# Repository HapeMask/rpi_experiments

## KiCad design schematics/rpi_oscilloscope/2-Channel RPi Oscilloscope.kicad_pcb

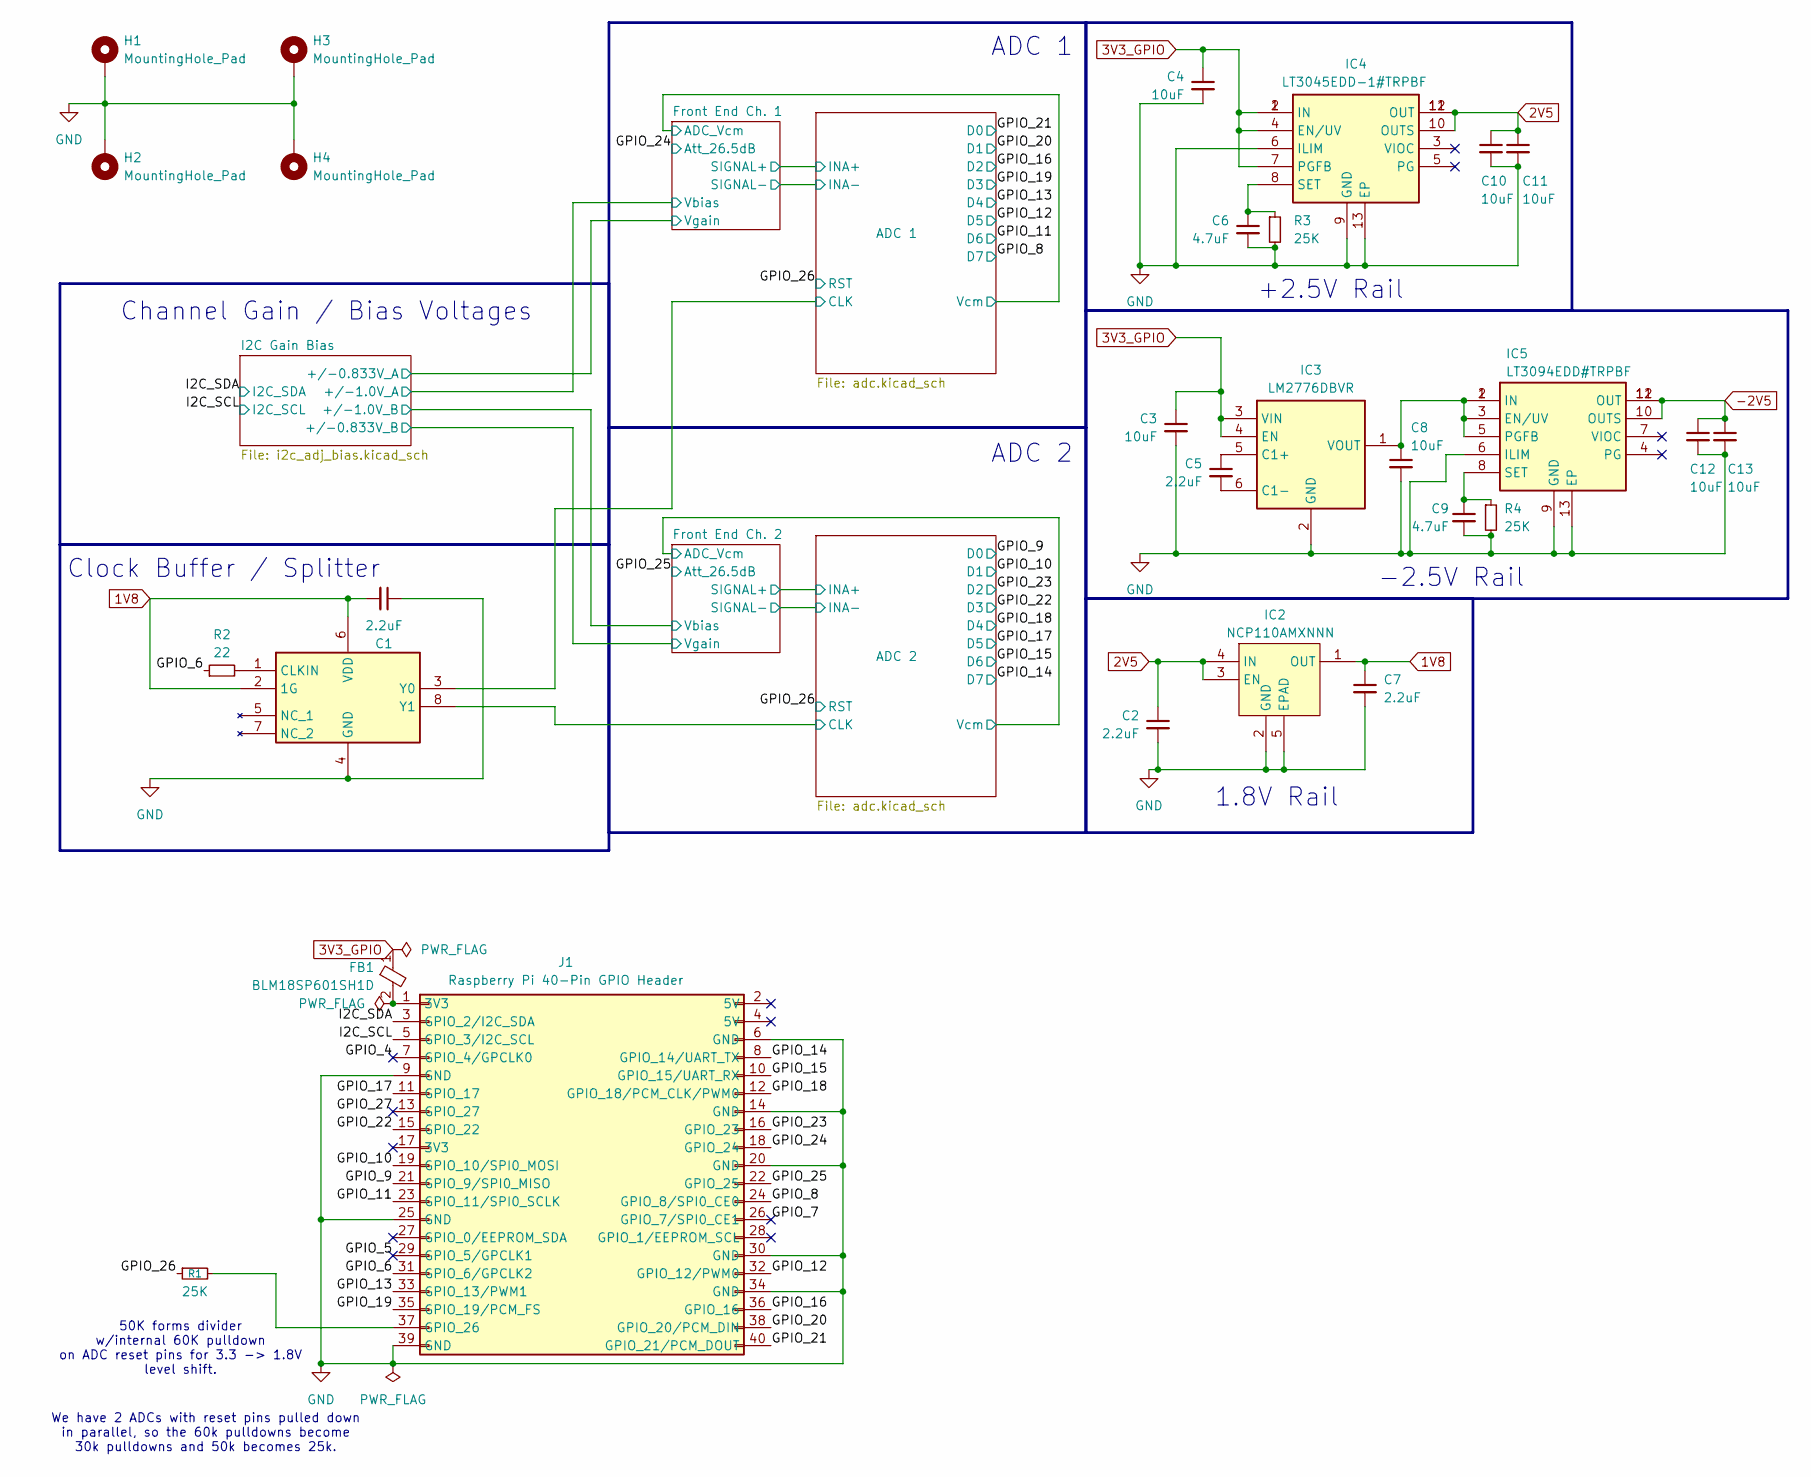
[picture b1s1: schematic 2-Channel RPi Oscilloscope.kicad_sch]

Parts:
C1, C2, C5, C7: 2.2uF; C_0805_2012Metric
C3, C4, C8, C10, C11, C12, C13: 10uF; C_0805_2012Metric; Manufacturer_Part_Number CL21B106KOQNNNE
C6, C9: 4.7uF; C_0805_2012Metric; Manufacturer_Part_Number GRM21BR71C475ME51K
FB1: BLM18SP601SH1D; BLM18SP221SN1B; Manufacturer_Part_Number BLM18SP601SH1D; Mouser Part Number 81-BLM18SP601SH1D
H1, H2, H3, H4: MountingHole_Pad; MountingHole_3mm_Pad_TopBottom
IC1: LMK1C1102PWR; SOP65P640X120-8N; Manufacturer_Part_Number LMK1C1102PWR; Mouser Part Number 595-LMK1C1102PWR
IC2: NCP110AMXNNN; OnSemi_XDFN4-1EP_1.0x1.0mm_EP0.52x0.52mm; Manufacturer_Part_Number NCP110AMX180TBG
IC3: LM2776DBVR; SOT95P280X145-6N; Manufacturer_Part_Number LM2776DBVR; Mouser Part Number 595-LM2776DBVR
IC4: LT3045EDD-1#TRPBF; SON45P300X300X80-13N-D; Manufacturer_Part_Number LT3045EDD-1#TRPBF; Mouser Part Number 584-LT3045EDD-1TRPBF
IC5: LT3094EDD#TRPBF; SON45P300X300X80-13N-D; Manufacturer_Part_Number LT3094EDD#TRPBF; Mouser Part Number 584-LT3094EDD#TRPBF
J1: Raspberry Pi 40-Pin GPIO Header; PinSocket_2x20_P2.54mm_Vertical
R1: 25K; R_0805_2012Metric
R2: 22; R_0805_2012Metric; Manufacturer_Part_Number RS73G2ATTD22R0B
R3, R4: 25K; R_0805_2012Metric; Manufacturer_Part_Number CPF-A-0805B25KE

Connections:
1V8: C1.2, C7.1, IC1.2 (1G), IC1.6 (VDD), IC2.1 (OUT); also elsewhere on the board
2V5: C2.1, C10.1, C11.1, IC2.3 (EN), IC2.4 (IN), IC4.10 (OUTS), IC4.11 (OUT), IC4.12 (OUT); also elsewhere on the board
3V3_GPIO: C3.1, C4.1, FB1.1, IC3.3 (VIN), IC3.4 (EN), IC4.1 (IN), IC4.2 (IN), IC4.4 (EN/UV), IC4.7 (PGFB); also elsewhere on the board
-2V5: C12.1, C13.1, IC5.10 (OUTS), IC5.11 (OUT), IC5.12 (OUT); also elsewhere on the board
/ADC 1/CLK: IC1.3 (Y0); also elsewhere on the board
/ADC 2/CLK: IC1.8 (Y1); also elsewhere on the board
/GPIO_4: J1.7 (GPIO_4/GPCLK0)
/GPIO_5: J1.29 (GPIO_5/GPCLK1)
/GPIO_6: J1.31 (GPIO_6/GPCLK2), R2.1
/GPIO_7: J1.26 (GPIO_7/SPI0_CE1)
/GPIO_8: J1.24 (GPIO_8/SPI0_CE0); also elsewhere on the board
/GPIO_9: J1.21 (GPIO_9/SPI0_MISO); also elsewhere on the board
/GPIO_10: J1.19 (GPIO_10/SPI0_MOSI); also elsewhere on the board
/GPIO_11: J1.23 (GPIO_11/SPI0_SCLK); also elsewhere on the board
/GPIO_12: J1.32 (GPIO_12/PWM0); also elsewhere on the board
/GPIO_13: J1.33 (GPIO_13/PWM1); also elsewhere on the board
/GPIO_14: J1.8 (GPIO_14/UART_TX); also elsewhere on the board
/GPIO_15: J1.10 (GPIO_15/UART_RX); also elsewhere on the board
/GPIO_16: J1.36 (GPIO_16); also elsewhere on the board
/GPIO_17: J1.11 (GPIO_17); also elsewhere on the board
/GPIO_18: J1.12 (GPIO_18/PCM_CLK/PWM0); also elsewhere on the board
/GPIO_19: J1.35 (GPIO_19/PCM_FS); also elsewhere on the board
/GPIO_20: J1.38 (GPIO_20/PCM_DIN); also elsewhere on the board
/GPIO_21: J1.40 (GPIO_21/PCM_DOUT); also elsewhere on the board
/GPIO_22: J1.15 (GPIO_22); also elsewhere on the board
/GPIO_23: J1.16 (GPIO_23); also elsewhere on the board
/GPIO_24: J1.18 (GPIO_24); also elsewhere on the board
/GPIO_25: J1.22 (GPIO_25); also elsewhere on the board
/GPIO_26: R1.1; also elsewhere on the board
/GPIO_27: J1.13 (GPIO_27)
/I2C_SCL: J1.5 (GPIO_3/I2C_SCL); also elsewhere on the board
/I2C_SDA: J1.3 (GPIO_2/I2C_SDA); also elsewhere on the board
GND: C1.1, C2.2, C3.2, C4.2, C6.2, C7.2, C8.2, C9.2, C10.2, C11.2, C12.2, C13.2, H1.1, H2.1, H3.1, H4.1, IC1.4 (GND), IC2.2 (GND), IC2.5 (EPAD), IC3.2 (GND), IC4.6 (ILIM), IC4.9 (GND), IC4.13 (EP), IC5.6 (ILIM), IC5.9 (GND), IC5.13 (EP), J1.6 (GND), J1.9 (GND), J1.14 (GND), J1.20 (GND), J1.25 (GND), J1.30 (GND), J1.34 (GND), J1.39 (GND), R3.2, R4.2; also elsewhere on the board
unnamed: FB1.2, J1.1 (3V3)
unnamed: IC1.1 (CLKIN), R2.2
unnamed: C5.1, IC3.5 (C1+)
unnamed: C5.2, IC3.6 (C1-)
unnamed: C8.1, IC3.1 (VOUT), IC5.1 (IN), IC5.2 (IN), IC5.3 (EN/UV), IC5.5 (PGFB)
unnamed: C6.1, IC4.8 (SET), R3.1
unnamed: C9.1, IC5.8 (SET), R4.1
unnamed: J1.37 (GPIO_26), R1.2

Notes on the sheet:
ADC 1
ADC 2
We have 2 ADCs with reset pins pulled down in parallel, so the 60k pulldowns become 30k pulldowns and 50k becomes 25k.
+2.5V Rail
-2.5V Rail
1.8V Rail
50K forms divider w/internal 60K pulldown on ADC reset pins for 3.3 -> 1.8V level shift.
Clock Buffer / Splitter
Channel Gain / Bias Voltages

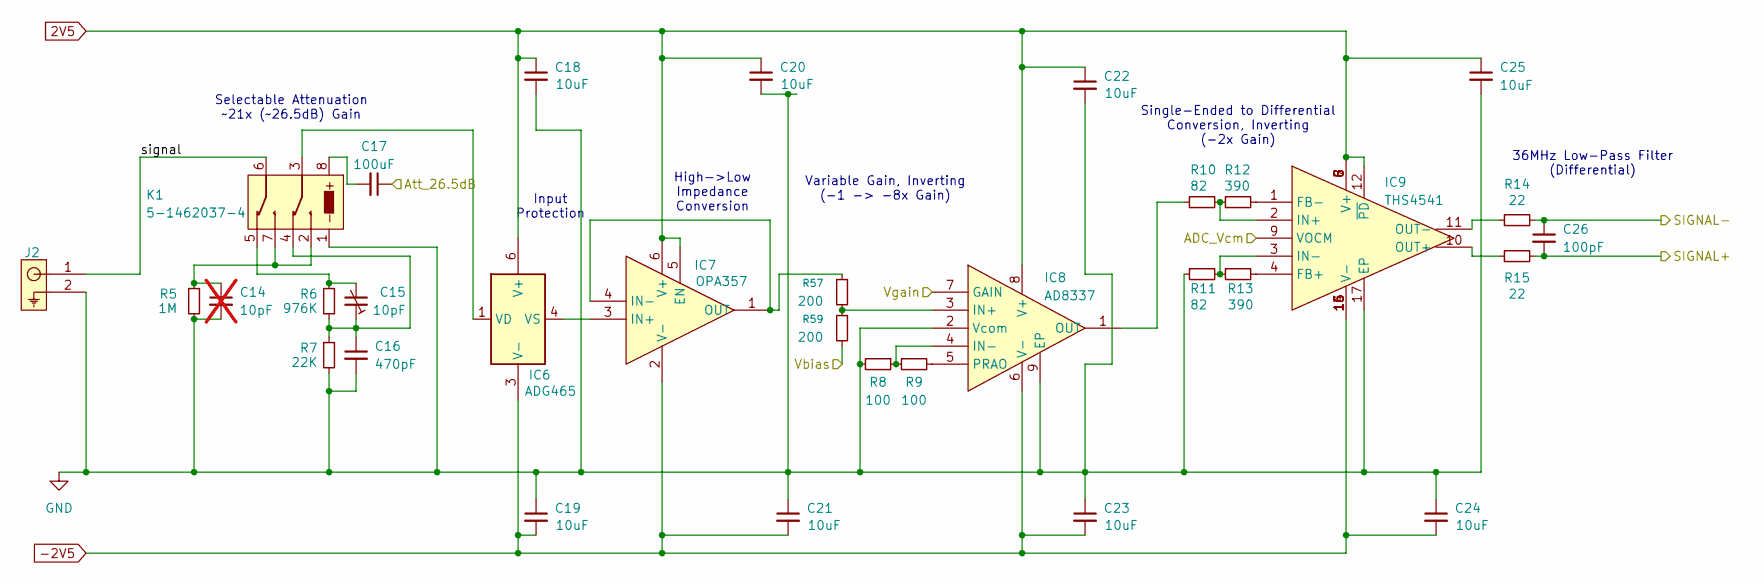
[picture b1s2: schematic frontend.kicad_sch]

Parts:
C14: 10pF; C_0805_2012Metric; not fitted
C15: 10pF; C_Trimmer_Sprague-Goodman_SGC3; Manufacturer_Part_Number SGC3S300
C16: 470pF; C_0805_2012Metric; Manufacturer_Part_Number GRM2165C1H201JA01D
C17: 100uF; C_1206_3216Metric; Manufacturer_Part_Number GRM31CR61A107MEA8L
C18, C19, C20, C21, C22, C23, C24, C25: 10uF; C_0805_2012Metric; Manufacturer_Part_Number CL21B106KOQNNNE
C26: 100pF; C_0805_2012Metric
IC6: ADG465; SOT95P280X145-6N; Manufacturer_Part_Number ADG465BRTZ-REEL7
IC7: OPA357; SOT95P280X145-6N; Manufacturer_Part_Number OPA357AIDBVR; Mouser Part Number 595-OPA357AIDBVR
IC8: AD8337; SON50P300X300X85-9N-D; Manufacturer_Part_Number AD8337BCPZ-REEL7; Mouser Part Number 584-AD8337BCPZ-R7
IC9: THS4541; QFN50P300X300X100-17N-D; Manufacturer_Part_Number THS4541IRGTR; Mouser Part Number 595-THS4541IRGTR
J2: 5-pin Coaxial Connector; 031_5431_10RFX; Manufacturer_Part_Number 031-5431-10RFX
K1: 5-1462037-4; 514620374; Manufacturer_Part_Number 5-1462037-4; Mouser Part Number 655-5-1462037-4
R5: 1M; R_0805_2012Metric
R6: 976K; R_0805_2012Metric
R7: 22K; R_0805_2012Metric
R8, R9: 100; R_0805_2012Metric
R10, R11: 82; R_0805_2012Metric
R12, R13: 390; R_0805_2012Metric
R14, R15: 22; R_0805_2012Metric; Manufacturer_Part_Number RS73G2ATTD22R0B
R57, R59: 200; R_0805_2012Metric

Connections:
2V5: C18.1, C20.1, C22.1, C25.1, IC6.6 (V+), IC7.5 (EN), IC7.6 (V+), IC8.8 (V+), IC9.5 (V+), IC9.6 (V+), IC9.7 (V+), IC9.8 (V+), IC9.12 (~PD); also elsewhere on the board
-2V5: C19.2, C21.2, C23.2, C24.2, IC6.3 (V-), IC7.2 (V-), IC8.6 (V-), IC9.13 (V-), IC9.14 (V-), IC9.15 (V-), IC9.16 (V-); also elsewhere on the board
/ADC 1/INA+: C26.2, R15.2; also elsewhere on the board
/ADC 1/INA-: C26.1, R14.2; also elsewhere on the board
/ADC 1/Vcm: IC9.9 (VOCM); also elsewhere on the board
/Front End Ch. 1/Vbias: R59.2; also elsewhere on the board
/Front End Ch. 1/Vgain: IC8.7 (GAIN); also elsewhere on the board
/Front End Ch. 1/signal: J2.1, K1.6
/GPIO_24: C17.1; also elsewhere on the board
GND: C14.2, C16.2, C18.2, C19.1, C20.2, C21.1, C22.2, C23.1, C24.1, C25.2, IC8.2 (Vcom), IC8.9 (EP), IC9.17 (EP), J2.2, K1.1, R5.2, R7.2, R8.2, R11.1; also elsewhere on the board
unnamed: C14.1, K1.2, K1.7, R5.1
unnamed: C15.1, C16.1, K1.4, R6.2, R7.1
unnamed: C15.2, K1.5, R6.1
unnamed: C17.2, K1.8
unnamed: IC6.1 (VD), K1.3
unnamed: IC6.4 (VS), IC7.3 (IN+)
unnamed: IC7.1 (OUT), IC7.4 (IN-), R57.1
unnamed: IC8.3 (IN+), R57.2, R59.1
unnamed: IC8.4 (IN-), R8.1, R9.1
unnamed: IC8.1 (OUT), R10.1
unnamed: IC8.5 (PRAO), R9.2
unnamed: IC9.4 (FB+), R13.2
unnamed: IC9.1 (FB-), R12.2
unnamed: IC9.2 (IN+), R10.2, R12.1
unnamed: IC9.3 (IN-), R11.2, R13.1
unnamed: IC9.10 (OUT+), R15.1
unnamed: IC9.11 (OUT-), R14.1

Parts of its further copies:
C27: 10pF; C_0805_2012Metric; not fitted
C28: 10pF; C_Trimmer_Sprague-Goodman_SGC3; Manufacturer_Part_Number SGC3S300
C29: 470pF; C_0805_2012Metric; Manufacturer_Part_Number GRM2165C1H201JA01D
C30: 100uF; C_1206_3216Metric; Manufacturer_Part_Number GRM31CR61A107MEA8L
C31, C32, C33, C34, C35, C36, C37, C38: 10uF; C_0805_2012Metric; Manufacturer_Part_Number CL21B106KOQNNNE
C39: 100pF; C_0805_2012Metric
IC10: ADG465; SOT95P280X145-6N; Manufacturer_Part_Number ADG465BRTZ-REEL7
IC11: OPA357; SOT95P280X145-6N; Manufacturer_Part_Number OPA357AIDBVR; Mouser Part Number 595-OPA357AIDBVR
IC12: AD8337; SON50P300X300X85-9N-D; Manufacturer_Part_Number AD8337BCPZ-REEL7; Mouser Part Number 584-AD8337BCPZ-R7
IC13: THS4541; QFN50P300X300X100-17N-D; Manufacturer_Part_Number THS4541IRGTR; Mouser Part Number 595-THS4541IRGTR
J3: 5-pin Coaxial Connector; 031_5431_10RFX; Manufacturer_Part_Number 031-5431-10RFX
K2: 5-1462037-4; 514620374; Manufacturer_Part_Number 5-1462037-4; Mouser Part Number 655-5-1462037-4
R16: 1M; R_0805_2012Metric
R17: 976K; R_0805_2012Metric
R18: 22K; R_0805_2012Metric
R19, R20: 100; R_0805_2012Metric
R21, R22: 82; R_0805_2012Metric
R23, R24: 390; R_0805_2012Metric
R25, R26: 22; R_0805_2012Metric; Manufacturer_Part_Number RS73G2ATTD22R0B
R58, R60: 200; R_0805_2012Metric

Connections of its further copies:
2V5: C31.1, C33.1, C35.1, C38.1, IC10.6 (V+), IC11.5 (EN), IC11.6 (V+), IC12.8 (V+), IC13.5 (V+), IC13.6 (V+), IC13.7 (V+), IC13.8 (V+), IC13.12 (~PD); also elsewhere on the board
-2V5: C32.2, C34.2, C36.2, C37.2, IC10.3 (V-), IC11.2 (V-), IC12.6 (V-), IC13.13 (V-), IC13.14 (V-), IC13.15 (V-), IC13.16 (V-); also elsewhere on the board
/ADC 2/INA+: C39.2, R26.2; also elsewhere on the board
/ADC 2/INA-: C39.1, R25.2; also elsewhere on the board
/ADC 2/Vcm: IC13.9 (VOCM); also elsewhere on the board
/Front End Ch. 2/Vbias: R60.2; also elsewhere on the board
/Front End Ch. 2/Vgain: IC12.7 (GAIN); also elsewhere on the board
/Front End Ch. 2/signal: J3.1, K2.6
/GPIO_25: C30.1; also elsewhere on the board
GND: C27.2, C29.2, C31.2, C32.1, C33.2, C34.1, C35.2, C36.1, C37.1, C38.2, IC12.2 (Vcom), IC12.9 (EP), IC13.17 (EP), J3.2, K2.1, R16.2, R18.2, R19.2, R22.1; also elsewhere on the board
unnamed: C27.1, K2.2, K2.7, R16.1
unnamed: C28.1, C29.1, K2.4, R17.2, R18.1
unnamed: C28.2, K2.5, R17.1
unnamed: C30.2, K2.8
unnamed: IC10.1 (VD), K2.3
unnamed: IC10.4 (VS), IC11.3 (IN+)
unnamed: IC11.1 (OUT), IC11.4 (IN-), R58.1
unnamed: IC12.3 (IN+), R58.2, R60.1
unnamed: IC12.4 (IN-), R19.1, R20.1
unnamed: IC12.1 (OUT), R21.1
unnamed: IC12.5 (PRAO), R20.2
unnamed: IC13.4 (FB+), R24.2
unnamed: IC13.1 (FB-), R23.2
unnamed: IC13.2 (IN+), R21.2, R23.1
unnamed: IC13.3 (IN-), R22.2, R24.1
unnamed: IC13.10 (OUT+), R26.1
unnamed: IC13.11 (OUT-), R25.1

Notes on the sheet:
Input Protection
Single-Ended to Differential Conversion, Inverting (-2x Gain)
High->Low Impedance Conversion
36MHz Low-Pass Filter (Differential)
Selectable Attenuation ~21x (~26.5dB) Gain
Variable Gain, Inverting (-1 -> -8x Gain)

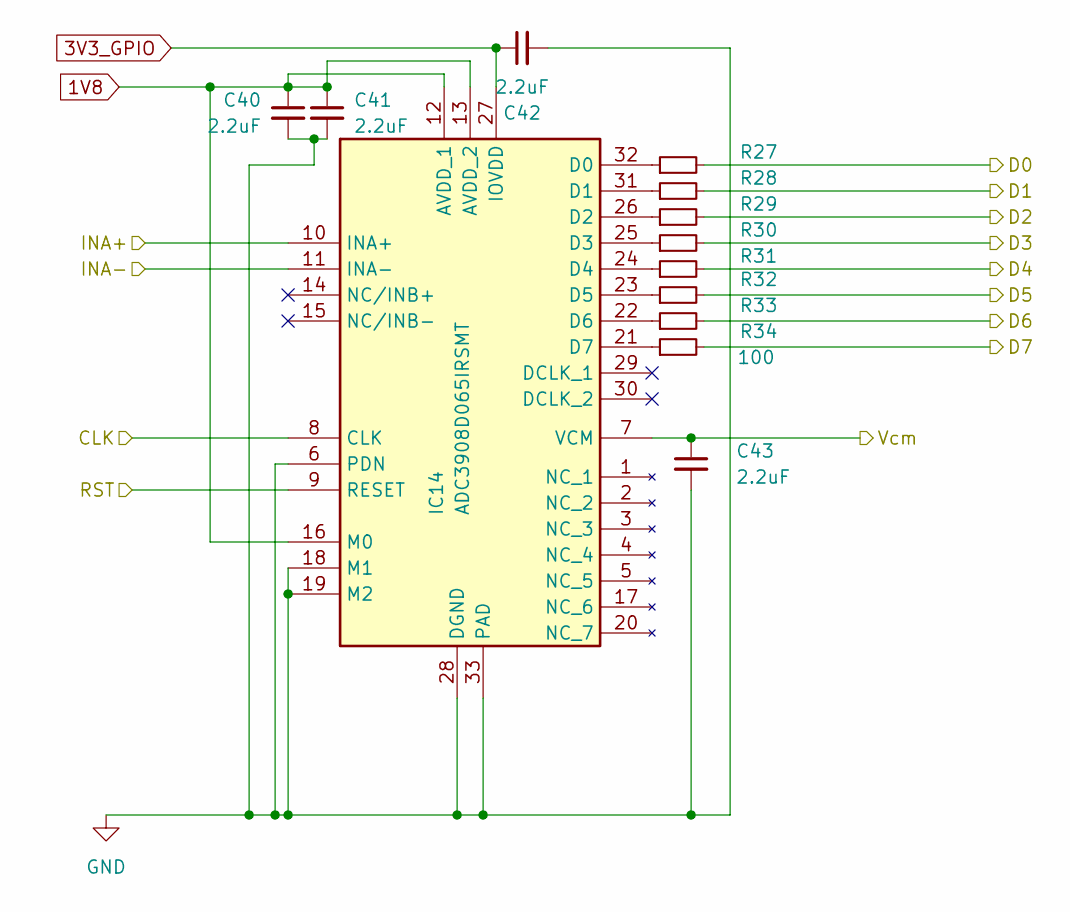
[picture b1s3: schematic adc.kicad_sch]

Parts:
C40, C41, C42, C43: 2.2uF; C_0805_2012Metric
IC14: ADC3908D065IRSMT; QFN40P400X400X100-33N-D; Manufacturer_Part_Number ADC3908D065IRSMT
R27, R28, R29, R30, R31, R32, R33, R34: 100; R_0805_2012Metric; Manufacturer_Part_Number RS73G2ATTD22R0B

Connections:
1V8: C40.1, C41.1, IC14.12 (AVDD_1), IC14.13 (AVDD_2), IC14.16 (M0); also elsewhere on the board
3V3_GPIO: C42.1, IC14.27 (IOVDD); also elsewhere on the board
/ADC 1/CLK: IC14.8 (CLK); also elsewhere on the board
/ADC 1/INA+: IC14.10 (INA+); also elsewhere on the board
/ADC 1/INA-: IC14.11 (INA-); also elsewhere on the board
/ADC 1/Vcm: C43.1, IC14.7 (VCM); also elsewhere on the board
/GPIO_8: R34.2; also elsewhere on the board
/GPIO_11: R33.2; also elsewhere on the board
/GPIO_12: R32.2; also elsewhere on the board
/GPIO_13: R31.2; also elsewhere on the board
/GPIO_16: R29.2; also elsewhere on the board
/GPIO_19: R30.2; also elsewhere on the board
/GPIO_20: R28.2; also elsewhere on the board
/GPIO_21: R27.2; also elsewhere on the board
/GPIO_26: IC14.9 (RESET); also elsewhere on the board
GND: C40.2, C41.2, C42.2, C43.2, IC14.6 (PDN), IC14.18 (M1), IC14.19 (M2), IC14.28 (DGND), IC14.33 (PAD); also elsewhere on the board
unnamed: IC14.32 (D0), R27.1
unnamed: IC14.31 (D1), R28.1
unnamed: IC14.26 (D2), R29.1
unnamed: IC14.25 (D3), R30.1
unnamed: IC14.24 (D4), R31.1
unnamed: IC14.23 (D5), R32.1
unnamed: IC14.22 (D6), R33.1
unnamed: IC14.21 (D7), R34.1

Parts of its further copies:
C44, C45, C46, C47: 2.2uF; C_0805_2012Metric
IC15: ADC3908D065IRSMT; QFN40P400X400X100-33N-D; Manufacturer_Part_Number ADC3908D065IRSMT
R35, R36, R37, R38, R39, R40, R41, R42: 100; R_0805_2012Metric; Manufacturer_Part_Number RS73G2ATTD22R0B

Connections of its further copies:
1V8: C44.1, C45.1, IC15.12 (AVDD_1), IC15.13 (AVDD_2), IC15.16 (M0); also elsewhere on the board
3V3_GPIO: C46.1, IC15.27 (IOVDD); also elsewhere on the board
/ADC 2/CLK: IC15.8 (CLK); also elsewhere on the board
/ADC 2/INA+: IC15.10 (INA+); also elsewhere on the board
/ADC 2/INA-: IC15.11 (INA-); also elsewhere on the board
/ADC 2/Vcm: C47.1, IC15.7 (VCM); also elsewhere on the board
/GPIO_9: R35.2; also elsewhere on the board
/GPIO_10: R36.2; also elsewhere on the board
/GPIO_14: R42.2; also elsewhere on the board
/GPIO_15: R41.2; also elsewhere on the board
/GPIO_17: R40.2; also elsewhere on the board
/GPIO_18: R39.2; also elsewhere on the board
/GPIO_22: R38.2; also elsewhere on the board
/GPIO_23: R37.2; also elsewhere on the board
/GPIO_26: IC15.9 (RESET); also elsewhere on the board
GND: C44.2, C45.2, C46.2, C47.2, IC15.6 (PDN), IC15.18 (M1), IC15.19 (M2), IC15.28 (DGND), IC15.33 (PAD); also elsewhere on the board
unnamed: IC15.32 (D0), R35.1
unnamed: IC15.31 (D1), R36.1
unnamed: IC15.26 (D2), R37.1
unnamed: IC15.25 (D3), R38.1
unnamed: IC15.24 (D4), R39.1
unnamed: IC15.23 (D5), R40.1
unnamed: IC15.22 (D6), R41.1
unnamed: IC15.21 (D7), R42.1

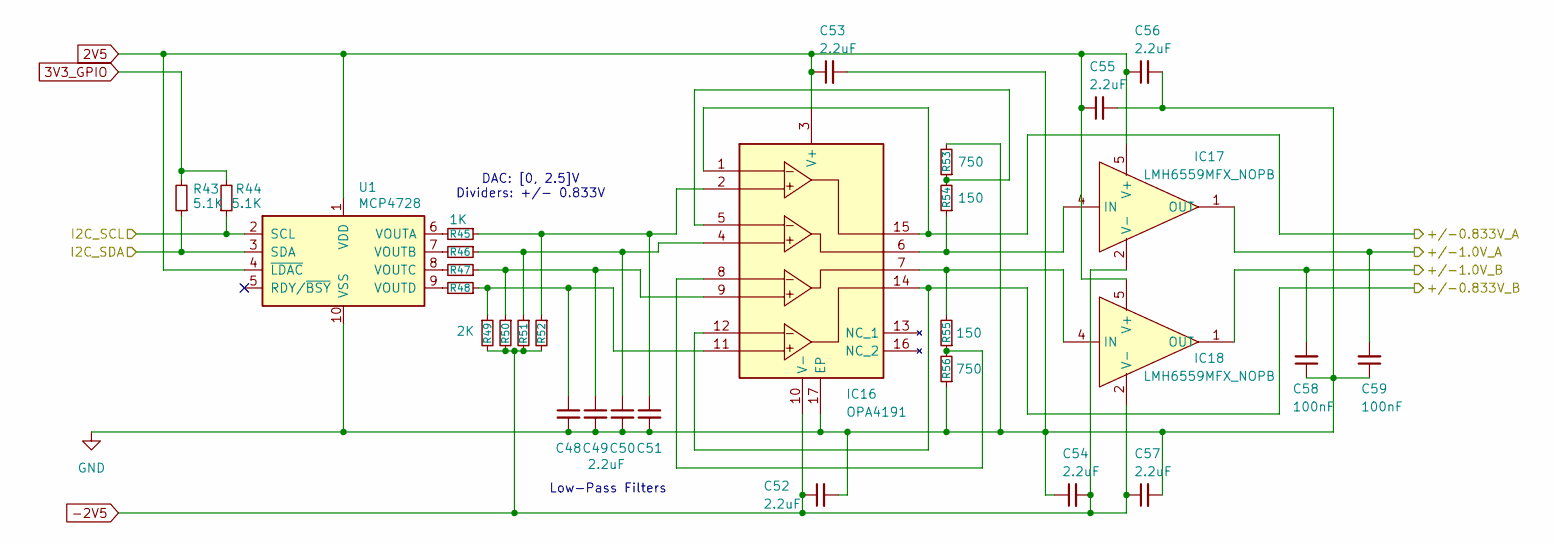
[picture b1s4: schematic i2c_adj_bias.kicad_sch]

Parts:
C48, C49, C50, C51, C52, C53, C54, C55, C56, C57: 2.2uF; C_0805_2012Metric
C58, C59: 100nF; C_0805_2012Metric
IC16: OPA4191; QFN65P400X400X80-17N-D; Manufacturer_Part_Number OPA4191IRUMR; Mouser Part Number 595-OPA4191IRUMR
IC17, IC18: LMH6559MFX_NOPB; SOT95P280X145-5N; Manufacturer_Part_Number LMH6559MFX/NOPB; Mouser Part Number 926-LMH6559MFX/NOPB
R43, R44: 5.1K; R_0805_2012Metric
R45, R46, R47, R48: 1K; R_0805_2012Metric
R49, R50, R51, R52: 2K; R_0805_2012Metric
R53, R56: 750; R_0805_2012Metric
R54, R55: 150; R_0805_2012Metric
U1: MCP4728; MSOP-10_3x3mm_P0.5mm; Manufacturer_Part_Number MCP4728T-E/UN

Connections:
2V5: C53.1, C55.1, C56.1, IC16.3 (V+), IC17.5 (V+), IC18.5 (V+), U1.1 (VDD), U1.4 (~LDAC); also elsewhere on the board
3V3_GPIO: R43.2, R44.2; also elsewhere on the board
-2V5: C52.1, C54.2, C57.1, IC16.10 (V-), IC17.2 (V-), IC18.2 (V-), R49.2, R50.2, R51.2, R52.2; also elsewhere on the board
/Front End Ch. 1/Vbias: C59.2, IC17.1 (OUT); also elsewhere on the board
/Front End Ch. 1/Vgain: IC16.1, IC16.15; also elsewhere on the board
/Front End Ch. 2/Vbias: C58.2, IC18.1 (OUT); also elsewhere on the board
/Front End Ch. 2/Vgain: IC16.12, IC16.14; also elsewhere on the board
/I2C_SCL: R44.1, U1.2 (SCL); also elsewhere on the board
/I2C_SDA: R43.1, U1.3 (SDA); also elsewhere on the board
GND: C48.2, C49.2, C50.2, C51.2, C52.2, C53.2, C54.1, C55.2, C56.2, C57.2, C58.1, C59.1, IC16.17 (EP), R53.2, R56.1, U1.10 (VSS); also elsewhere on the board
unnamed: C48.1, IC16.11, R48.1, R49.1
unnamed: C49.1, IC16.9, R47.1, R50.1
unnamed: C50.1, IC16.4, R46.1, R51.1
unnamed: C51.1, IC16.2, R45.1, R52.1
unnamed: IC16.5, R53.1, R54.2
unnamed: IC16.8, R55.1, R56.2
unnamed: IC16.6, IC17.4 (IN), R54.1
unnamed: IC16.7, IC18.4 (IN), R55.2
unnamed: R45.2, U1.6 (VOUTA)
unnamed: R46.2, U1.7 (VOUTB)
unnamed: R47.2, U1.8 (VOUTC)
unnamed: R48.2, U1.9 (VOUTD)

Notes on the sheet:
Low-Pass Filters
DAC: [0, 2.5]V Dividers: +/- 0.833V

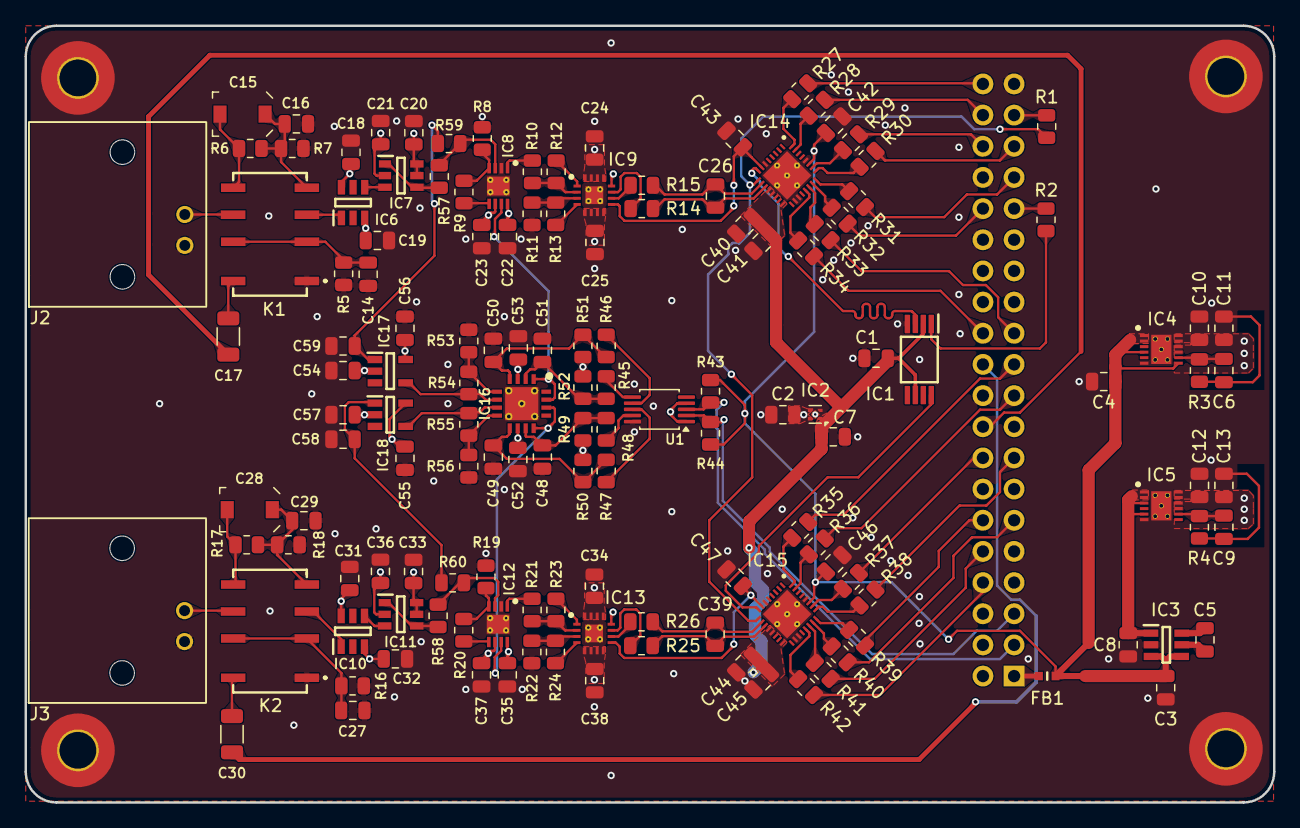
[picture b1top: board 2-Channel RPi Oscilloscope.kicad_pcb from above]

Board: 4 copper layers, 101.8 x 63.3 mm, 148 parts (1 on the bottom side), 111 nets.

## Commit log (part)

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2025-12-02 Add many icons, fix triggering auto range, add pan/zoom toggles.
2025-12-02 Remove some old test code.
2025-12-02 [clock] More clock refactoring. Move PWM duty/freq into setup clocks and don't call it automatically.
2025-12-02 [adc] Remove BufferedADC from python module, add interface for n_samples.
2025-12-02 [clock] Refactor clock interface to move more shared stuff into the Clock peripheral.
2025-12-02 [peripherals] Add SMI peripheral.
2025-12-02 [adc] Rename old "DMA ADC" to SerialADC.
2025-12-02 [smi] Finish SMI implementation. Initial version.
2025-12-02 [utils] Fix CMakeLists.txt still using OBJECT.
2025-12-02 Stop using #define where possible.
2025-12-02 [utils] Add PLLC clock frequency to HW-specific defs.
2025-12-02 Add new shared peripheral interface.
2025-12-02 [clock] Fix linkage issue w/clock library.
2025-12-02 Fix linkage issues by changing from object -> static libraries.
2025-12-02 Initial commit.
2025-12-02 [adc] Add new parallel ADC, support in python code, and multi-channel support.
2025-12-02 [clock] Fix lack of support for clock divider of 1 (it needs to be 0 when div is 1).
2025-12-02 Use uint32_t for constants.
2025-12-02 Replace VDD with more flexible VREF.
2025-12-02 Fix compiler warnings.
2025-12-03 Switch VREF to support new circuit changes.
2025-12-12 Add ability to change the sample buffer size from inside the app.
2026-01-02 Switch to hard-coded list of acceptable sample rates.
2026-01-02 Switch to a numpy array for internal sample storage to avoid copies and other conversions.
2026-01-02 Pass env vars to osc.bash to allow for profiling with LINE_PROFILING=1.
2026-01-02 Move triggering logic to C++ code.
2026-01-02 Fix bug that skipped the last sample when processing an odd number of samples.
2026-01-02 Fix issue resizing sample buffer after it has been returned at least once.
2026-01-02 Switch to PyQt6. Better support for dark mode and other things.
2026-01-02 Clean up sample rate / buffer size changing logic for channel toggling.
2026-01-05 Add adjustable trigger threshold, shown and controlled by a line.
2026-01-09 Add basic interface for MCP4728 DAC via I2C.
2026-01-09 Add multi-range DAC combining MCP4728 and MCP6489 for 2x bipolar and 2x negative channels.
2026-01-09 Expose GPIO peripheral to Python.
2026-01-09 Add dV/dt label to zoom rect for measurements.
2026-01-09 Switch threshold display toggle to push button for usability on touchscreens.
2026-01-09 Bring back SerialADC and update interface to be compatible with new UI.
2026-01-09 Rename ads7884 module to represent current contents (more ADCs).
2026-02-19 Add MCP4728 DAC interface.
2026-02-19 Make test frequency controlled via CLI.
2026-03-11 Refactor ADC classes to move shared code into a base class.
2026-03-11 Add binning down to screen width and anti-aliasing.
2026-03-17 Expose 'real' SPI clock speed.
2026-03-17 Add a frequency counter that uses SMI to read one of the GPIO pins rapidly.
2026-03-17 Add missing gpclk_test.cpp.
2026-03-17 Add T/p SI prefixes and scales.
2026-03-17 Add CLI input for frequency counter sample rate.
2026-03-17 Expose frequency counter to Python.
2026-03-17 Add initial implementation of LC meter.
2026-03-17 Split C++ python extension module into two modules, one for ADCs and one for peripherals.
2026-04-08 Add logic analyzer mode.
    This mode simply reads the GPIO level register as fast as possible
    w/DMA, and breaks the bits out into logic lines.
2026-04-08 Exposes logic analyzer mode and true multiple channel trace graphing to GUI.
2026-04-08 Logic analyzer mode uses chained DMA CBs with PWM gating to read at a fixed sample rate instead of whatever DMA can hit.
2026-04-08 Improve DMA wait behavior to adjust based on sample rate. Also add new very-slow sampling rates for LA mode in particular.
2026-04-08 Add threading support to C++ extension to stop blocking UI while the DMA transfers take place.
2026-04-08 Fix triggering offset caused by binning, also bug where updating wouldn't happen on startup.
2026-04-08 Fix unit prefixes.
2026-04-08 Make DMA wait failures only throw in debug builds.
2026-04-08 Make sure ADC stops when entering LA mode and restarts when exiting LA mode.
2026-04-13 Add real logic for ADC full scale ranges, gains, and biases. Move chip-specific logic into these new classes.
2026-04-13 Clean up sample buffer data structures. Improve binning to use screen X (time) range in addition to screen pixel width to determine samples per bin.
2026-04-13 Let user switch ADCs w/CLI flag.
2026-04-13 Add GPIO register push/pop mode mechanism and fix LA mode GPIO pins not being set to inputs.
2026-04-15 Add voltage range selection and associated DAC configuration.
2026-04-20 Make input FSR selectable per-channel, and correct trigger level (map it from real input range -> ADC FSR).
2026-04-20 Remove CSS and icons from buttons.
2026-04-20 Typing fixes and add pyproject.toml with mypy config.
2026-04-20 Make individual channels fully-configurable.
2026-04-20 Remove active-channel-count-dependent availablity of sample rates.
2026-04-20 Fix missing elif clause in get_si_prefixes.
2026-04-21 Code cleanup. Split __init__ into more methods. Add colors to channel enable buttons.
2026-04-21 Add VGA calibration factor, fix bugs in FSR range calculations.
2026-04-21 Resurrect ADS7884 in the new framework.
2026-04-22 Don't reset graph when changing channel configs.
2026-04-22 Add bias sliders (initial implementation, need to add FSR options for non-centered signals to maximize range via gain adjustment).
2026-06-03 Add 2ch. oscilloscope schematics.
